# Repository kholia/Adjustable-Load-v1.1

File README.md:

### Variable Electronic Load

This variable electronic load helps with testing power supplies, and batteries.

Motivation: RIGOL DC Electronic Load-DL3021 costs ~50k - this project costs
nothing in comparison, and does the job in typical amateur radio contexts just
fine.

Rating: 20A @ 30V depending upon the heatsink.

Testing notes (Dhiru): I have tested my build up to 5A @ around 20v.

This is an improved version of https://www.instructables.com/DIY-Adjustable-Constant-Load-Current-Power/. All
credit goes to `GreatScott` for coming up with this project.

Note: The 3D renderings are *only* published to help with the manual layout work on
Zero-PCBs. All screenshots are clickable and zoomable.

See `Adjustable-Load-v1.1.pdf` for details.

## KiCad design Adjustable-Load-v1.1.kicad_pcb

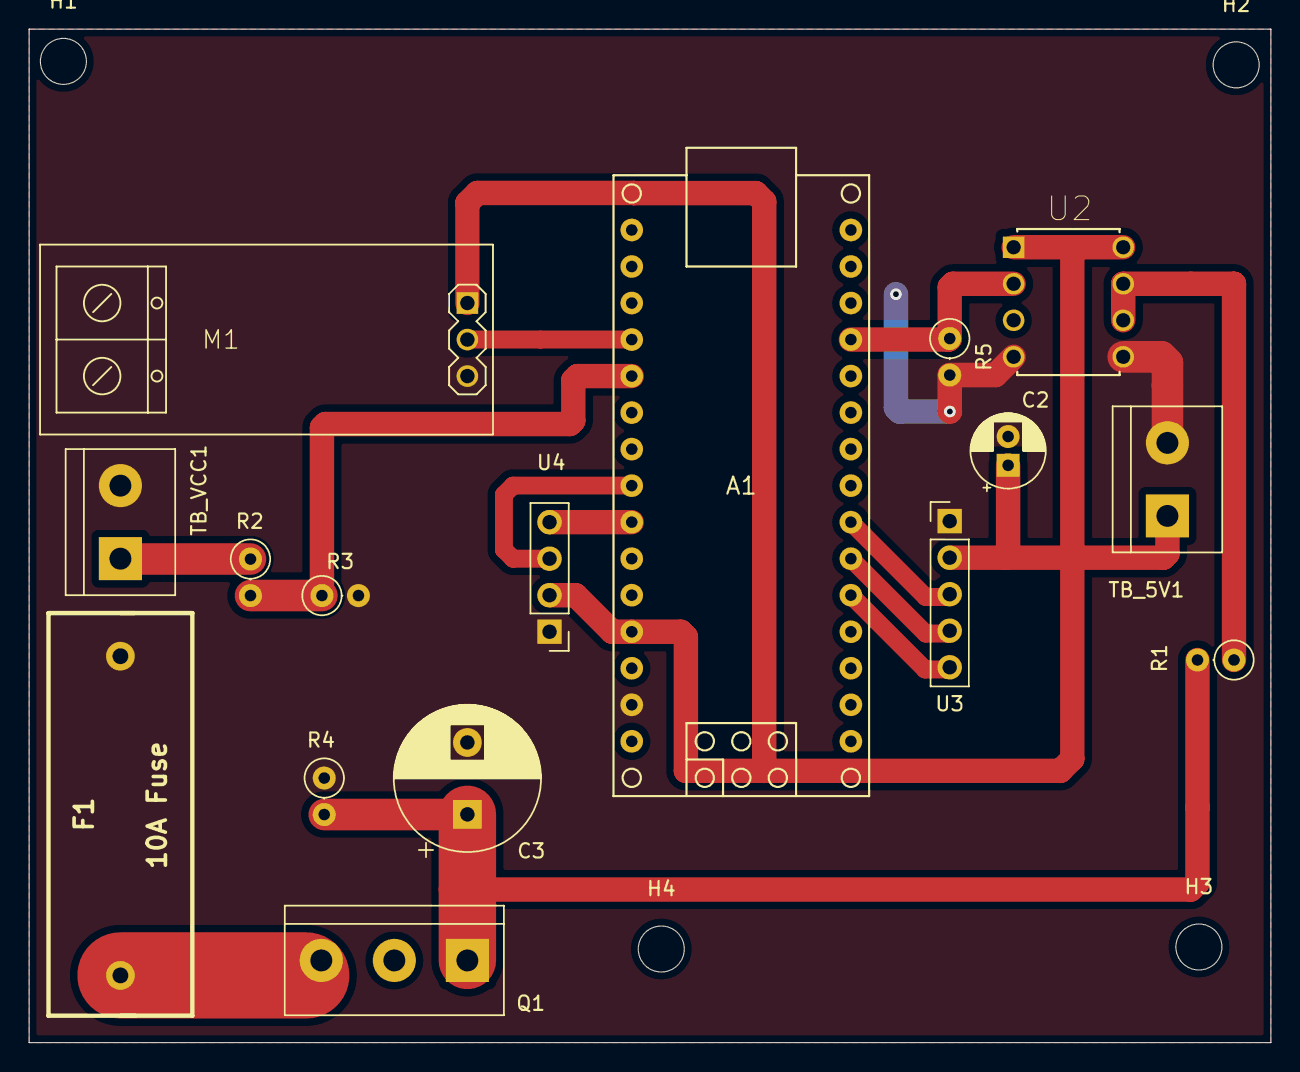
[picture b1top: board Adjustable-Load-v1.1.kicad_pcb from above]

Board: 2 copper layers, 86.4 x 70.5 mm, 20 parts (0 on the bottom side), 14 nets.

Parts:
A1: Arduino_Nano; arduino_nano
C2: 22uF; CP_Radial_D5.0mm_P2.00mm
C3: 470uF; CP_Radial_D10.0mm_P5.00mm
F1: 10A Fuse; BLX-A
H1, H2, H3, H4: MountingHole; MountingHole_3.2mm_M3
M1: CURRENT-SENSOR-ACS712
Q1: IRFZ44NPBF; TerminalBlock_bornier-3_P5.08mm
R1: 10; R_Axial_DIN0207_L6.3mm_D2.5mm_P2.54mm_Vertical
R2: 10k; R_Axial_DIN0207_L6.3mm_D2.5mm_P2.54mm_Vertical
R3: 2k; R_Axial_DIN0207_L6.3mm_D2.5mm_P2.54mm_Vertical
R4: 150k; R_Axial_DIN0207_L6.3mm_D2.5mm_P2.54mm_Vertical
R5: 1k; R_Axial_DIN0207_L6.3mm_D2.5mm_P2.54mm_Vertical
TB_5V1: Screw_Terminal; TerminalBlock_bornier-2_P5.08mm
TB_VCC1: Screw_Terminal; TerminalBlock_bornier-2_P5.08mm
U2: TC4420CPA; DIP254P762X533-8
U3: Rotary_Encoder; PinHeader_1x05_P2.54mm_Vertical
U4: I2C-LCD-16X2; PinHeader_1x04_P2.54mm_Vertical

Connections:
+5V: A1.27 (5V), C2.1, M1.1 (5V), TB_5V1.1, U2.1 (VDD_2), U2.8 (VDD), U3.2 (VCC), U4.2 (VCC)
GND: A1.29 (GND), C2.2, C3.2, F1.1, M1.3 (GND), R3.2, R4.1, R5.2, TB_5V1.2, TB_VCC1.2, U2.4 (GND_2), U2.5 (GND), U3.1 (GND), U4.1 (GND)
unnamed: A1.5 (D2), U3.5 (CLK)
unnamed: A1.6 (D3), U3.4 (DT)
unnamed: A1.7 (D4), U3.3 (SW)
unnamed: A1.12 (D9), R5.1, U2.2 (INPUT)
unnamed: A1.19 (A0), M1.2 (OUT_SIGNAL)
unnamed: A1.20 (A1), R2.2, R3.1
unnamed: A1.23 (A4), U4.3 (SDA)
unnamed: A1.24 (A5), U4.4 (SCL)
unnamed: C3.1, Q1.1, R1.2, R4.2
unnamed: F1.2, Q1.3
unnamed: R1.1, U2.6 (OUTPUT_2), U2.7 (OUTPUT)
VCC: R2.1, TB_VCC1.1

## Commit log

2022-02-25 Hello!
